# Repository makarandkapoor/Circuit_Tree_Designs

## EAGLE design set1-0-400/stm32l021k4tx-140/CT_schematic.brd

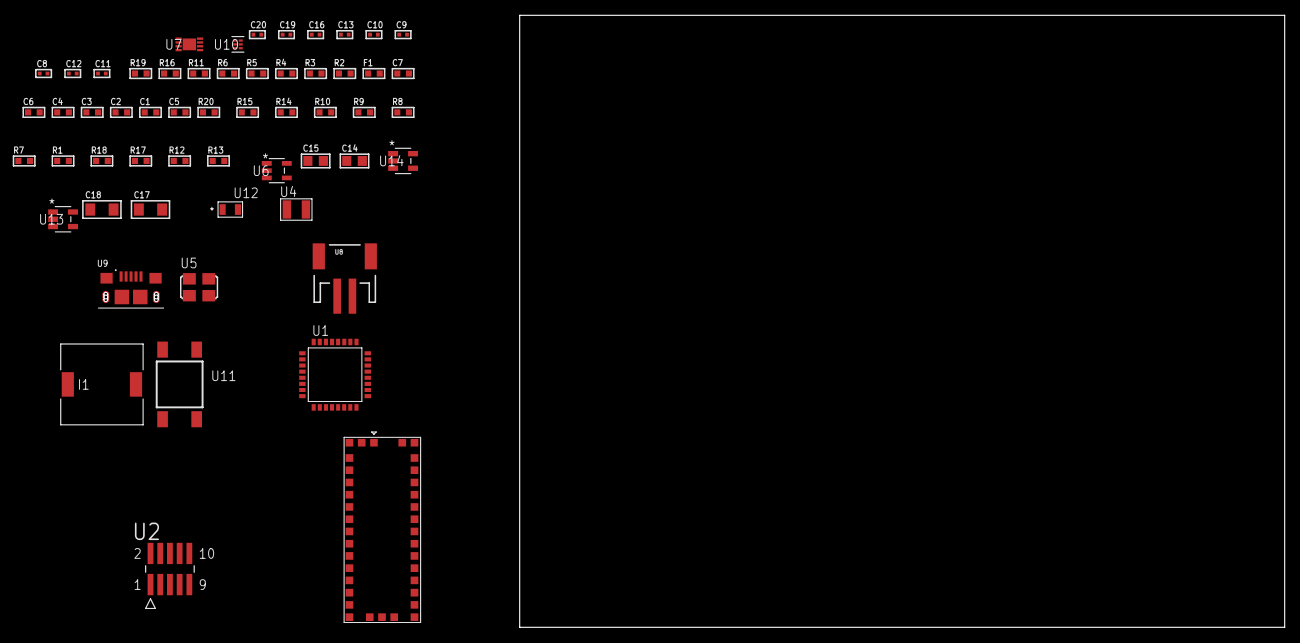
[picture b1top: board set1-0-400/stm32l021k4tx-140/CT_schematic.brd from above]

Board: 2 copper layers, 154.3 x 80.0 mm, 56 parts (0 on the bottom side), 26 nets, no tracks yet.

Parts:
C1, C2, C3, C4: 1e-07; C0603
C5: 4.7e-06; C0603
C6: 1e-08; C0603
C7: 1e-06; C0603
C8, C9: 1e-11; C0402
C10, C16: 1e-07; C0402
C11, C12: 2.2e-11; C0402
C13, C19, C20: 1e-08; C0402
C14, C15: 1e-05; C0805
C17, C18: 1e-05; C1206
F1: 240.0; L0603
I1: 3.8e-06; DR1040
R1, R7, R8, R9, R10, R14, R15, R20: 10000.0; R0603
R2: 1000.0; R0603
R3: 1600.5; R0603
R4: 4700.0; R0603
R5, R6: 2200.0; R0603
R11: 5.0; R0603
R12: 220000.0; R0603
R13: 1000000.0; R0603
R16: 9100.0; R0603
R17: 680000.0; R0603
R18: 120000.0; R0603
R19: 2000.0; R0603
U1: STM32L021K4T6; LQFP32
U2: FTSH-105-01-L-DV-K; SAMTEC_FTSH-105-01-L-DV-K
U3: M10382
U4: ABS07-32.768KHZ-7-T
U5: ASFL1-12MHZ-NCS; ASFL1
U6: ltc3406es5; TSOT-23-5
U7: MCP73831T-2ACI/MC; DFN8_2X3MC
U8: S2B-PH-SM4-TB(LF)(SN); JST-2-SMD
U9: 10118193-0001LF; FCI_10118193-0001LF
U10: TPS3895ADRYR; SON-6
U11: 4-1437565-2; SW_4-1437565-2
U12: Q65110A2395; LGM67K-G1J2-24-Z
U13, U14: nc7sz125m5x; NC7SZ125M5X

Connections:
CLK_CRYSTAL_U1_2: C8.1, U1.2, U4.1
CLK_CRYSTAL_U1_3: C9.1, U1.3, U4.2
CLK_U1_6: U1.6, U5.3
GND: C1.2, C2.2, C3.2, C4.2, C5.2, C6.2, C7.2, C8.2, C9.2, C10.2, C11.2, C12.2, C13.2, C14.2, C15.1, C15.2, C16.2, C17.2, C18.2, C19.2, C20.2, R2.2, R7.2, R11.2, R12.2, R16.2, R18.2, R19.2, U1.16, U1.32, U2.3, U2.5, U3.2, U3.4, U3.14, U3.17, U3.21, U3.24, U3.26, U3.28, U3.33, U3.34, U3.35, U3.36, U5.2, U6.2, U7.6, U7.9, U8.2, U9.5, U9.6, U9.7, U9.8, U9.9, U10.2, U12.C, U13.2, U13.3, U14.1, U14.3
INPUT_USBPOWER_5V: C17.1, R20.2, U7.1, U7.2, U9.1
NET_U1_4: R4.1, U1.4, U14.4
NET_U1_5: C6.1, C7.1, F1.1, U1.5
NET_U1_10: R5.1, U1.10, U3.19
NET_U1_20: R6.1, U1.20, U3.18
NET_U1_30: R3.1, U1.30, U12.A
NET_U1_31: R1.1, R7.1, U1.31, U11.3, U11.4
NET_U2_9: R11.1, U2.9
NET_U6_3: I1.1, U6.3
NET_U6_5: R12.1, R13.1, U6.5
NET_U6_ATNET_3: I1.2, R13.2
NET_U7_5: R20.1, U7.5
NET_U7_8: R19.1, U7.8
NET_U10_1: R15.1, R16.1, U10.1
NET_U10_3: R17.2, R18.1, U10.3
NET_U10_4: R14.1, U10.4, U13.4, U14.2
NET_U11_1: R2.1, U11.1, U11.2
PROC_SYS_SWCLK: R9.1, U1.24, U2.4
PROC_SYS_SWDIO: R10.1, U1.23, U2.2
RST_OUT_U2_JTAG_RST_B: R8.1, U2.10, U13.1
VCC_S1_3V7: C14.1, C18.1, U6.4, U7.3, U7.4, U8.1
VCC_TIER1_3V3: C1.1, C2.1, C3.1, C4.1, C5.1, C10.1, C11.1, C12.1, C13.1, C15.2, C16.1, C19.1, C20.1, F1.2, I1.2, R1.2, R3.2, R4.2, R5.2, R6.2, R8.2, R9.2, R10.2, R13.2, R14.2, R15.2, R17.1, U1.1, U1.17, U2.1, U3.5, U3.25, U3.27, U5.4, U10.6, U13.5, U14.5

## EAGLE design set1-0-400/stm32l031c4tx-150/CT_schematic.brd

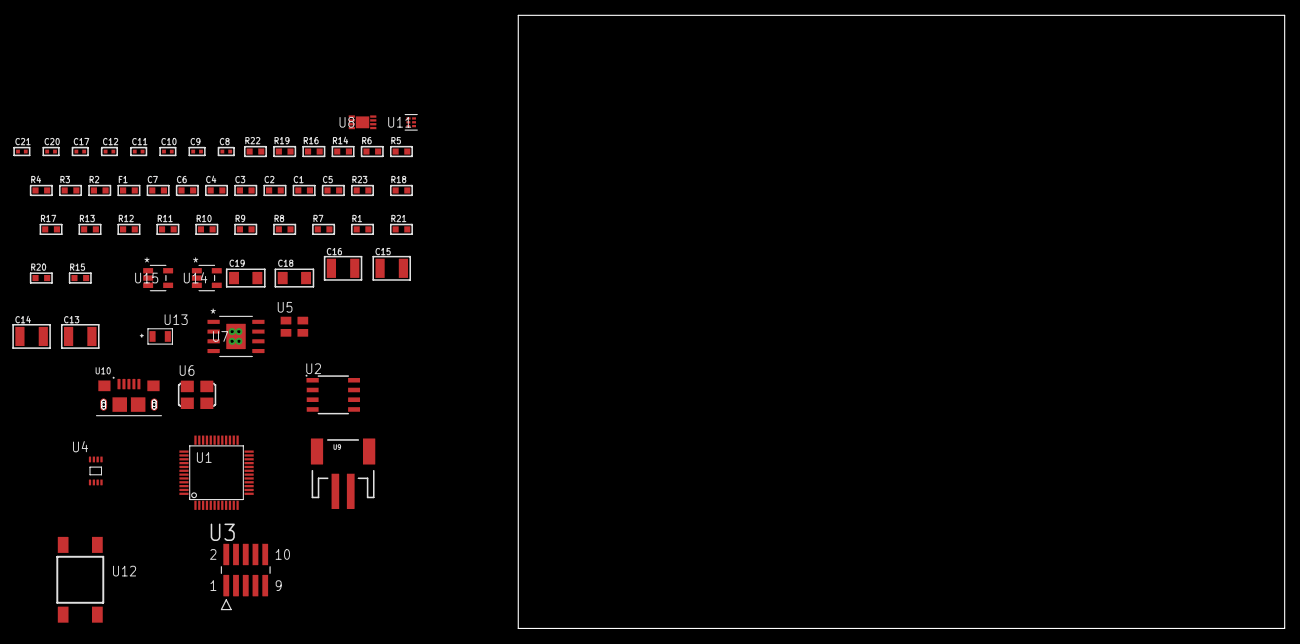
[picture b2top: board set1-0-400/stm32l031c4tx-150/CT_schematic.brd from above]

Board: 2 copper layers, 154.3 x 80.0 mm, 60 parts (0 on the bottom side), 30 nets, no tracks yet.

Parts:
C1, C2, C3, C4: 1e-07; C0603
C5: 4.7e-06; C0603
C6: 1e-08; C0603
C7: 1e-06; C0603
C8, C10, C11, C12, C20, C21: 1e-08; C0402
C9, C17: 1e-07; C0402
C13, C14, C15, C16: 1e-05; C1210
C18, C19: 1e-05; C1206
F1: 240.0; L0603
R1, R7, R8, R9, R10, R11, R12, R13, R17, R18, R23: 10000.0; R0603
R2: 1000.0; R0603
R3: 1600.5; R0603
R4: 4700.0; R0603
R5, R6, R16: 2200.0; R0603
R14: 5.0; R0603
R15: 4031.5447154472; R0603
R19: 9100.0; R0603
R20: 680000.0; R0603
R21: 120000.0; R0603
R22: 2000.0; R0603
U1: STM32L031C4T6; LQFP48
U2: AT25128B-SSHL-T; SOIC-8
U3: FTSH-105-01-L-DV-K; SAMTEC_FTSH-105-01-L-DV-K
U4: 24AA01T-I/MNY; TDFN-8/6MM
U5: ASEK-32.768KHz-ECST; ASEK
U6: ASFL1-25MHZ-NCS; ASFL1
U7: MIC5234YME; SOIC-8_EP
U8: MCP73831T-2ACI/MC; DFN8_2X3MC
U9: S2B-PH-SM4-TB(LF)(SN); JST-2-SMD
U10: 10118193-0001LF; FCI_10118193-0001LF
U11: TPS3895ADRYR; SON-6
U12: 4-1437565-2; SW_4-1437565-2
U13: Q65110A2395; LGM67K-G1J2-24-Z
U14, U15: nc7sz125m5x; NC7SZ125M5X

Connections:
CLK_U1_3: U1.3, U5.3
CLK_U1_5: U1.5, U6.3
GND: C1.2, C2.2, C3.2, C4.2, C5.2, C6.2, C7.2, C8.2, C9.2, C10.2, C11.2, C12.2, C13.2, C14.2, C15.2, C16.2, C17.2, C18.2, C19.2, C20.2, C21.2, R2.2, R7.2, R14.2, R16.2, R19.2, R21.2, R22.2, U1.8, U1.23, U1.35, U1.47, U2.4, U3.3, U3.5, U4.4, U4.7, U5.2, U6.2, U7.7, U7.EPAD, U8.6, U8.9, U9.2, U10.5, U10.6, U10.7, U10.8, U10.9, U11.2, U13.C, U14.2, U14.3, U15.1, U15.3
INPUT_USBPOWER_5V: C18.1, R23.2, U8.1, U8.2, U10.1
NET_U1_7: R4.1, U1.7, U15.4
NET_U1_9: C6.1, C7.1, F1.1, U1.9
NET_U1_30: R5.1, U1.30, U4.6
NET_U1_31: R6.1, U1.31, U4.5
NET_U1_44: R7.1, U1.44
NET_U1_45: R3.1, U1.45, U13.A
NET_U1_46: R1.1, U1.46, U12.3, U12.4
NET_U2_3: R8.1, U2.3
NET_U2_7: R10.1, U2.7
NET_U3_9: R14.1, U3.9
NET_U7_4: R15.2, R16.1, U7.4
NET_U8_5: R23.1, U8.5
NET_U8_8: R22.1, U8.8
NET_U11_1: R18.1, R19.1, U11.1
NET_U11_3: R20.2, R21.1, U11.3
NET_U11_4: R17.1, U11.4, U14.4, U15.2
NET_U12_1: R2.1, U12.1, U12.2
PROC_SPI1_MISO: U1.16, U2.2
PROC_SPI1_MOSI: U1.17, U2.5
PROC_SPI1_NSS: R9.1, U1.14, U2.1
PROC_SPI1_SCK: U1.15, U2.6
PROC_SYS_SWCLK: R12.1, U1.37, U3.4
PROC_SYS_SWDIO: R13.1, U1.34, U3.2
RST_OUT_U3_JTAG_RST_B: R11.1, U3.10, U14.1
VCC_S1_3V7: C13.1, C14.1, C19.1, U7.5, U7.8, U8.3, U8.4, U9.1
VCC_TIER1_3V3: C1.1, C2.1, C3.1, C4.1, C5.1, C8.1, C9.1, C10.1, C11.1, C12.1, C15.1, C16.1, C17.1, C20.1, C21.1, F1.2, R1.2, R3.2, R4.2, R5.2, R6.2, R8.2, R9.2, R10.2, R11.2, R12.2, R13.2, R15.1, R17.2, R18.2, R20.1, U1.24, U1.36, U1.48, U2.8, U3.1, U4.8, U5.4, U6.4, U7.1, U11.6, U14.5, U15.5

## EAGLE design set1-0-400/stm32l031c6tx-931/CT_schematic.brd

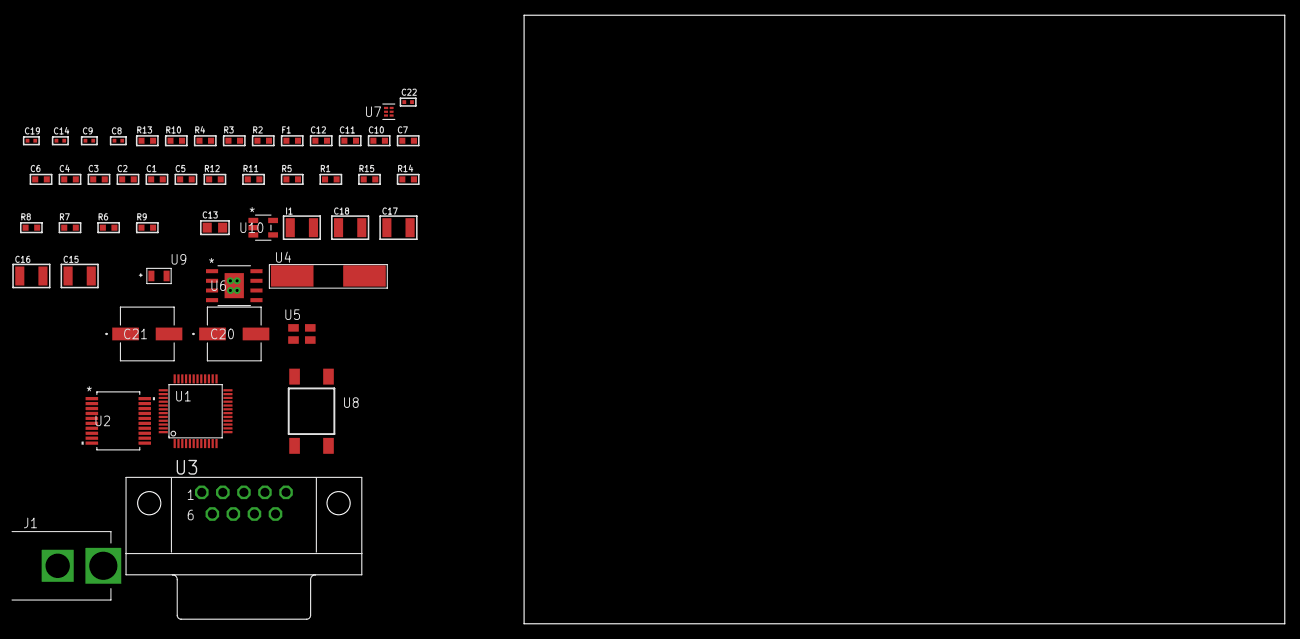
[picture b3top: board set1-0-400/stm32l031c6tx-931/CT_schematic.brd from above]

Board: 2 copper layers, 100.0 x 80.0 mm, 50 parts (0 on the bottom side), 32 nets, no tracks yet.

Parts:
C1, C2, C3, C4: 1e-07; C0603
C5: 4.7e-06; C0603
C6: 1e-08; C0603
C7, C10, C11, C12: 1e-06; C0603
C8, C9: 1e-11; C0402
C13: 4.7e-06; C0805
C14, C22: 1e-08; C0402
C15, C16, C17, C18: 1e-05; C1210
C19: 1e-07; C0402
C20, C21: 0.0001; EXV-9H
F1: 240.0; L0603
I1: 1.5e-05; L1210
J1: PJ-037B; PJ-037B_PACKAGE
R1, R5, R11, R12: 10000.0; R0603
R2: 1000.0; R0603
R3: 1600.5; R0603
R4: 4700.0; R0603
R6, R7, R8: 100000.0; R0603
R9: 4031.5447154472; R0603
R10: 2200.0; R0603
R13: 9100.0; R0603
R14: 680000.0; R0603
R15: 120000.0; R0603
U1: STM32L031C6T7; LQFP48
U2: MAX3218EAP+T; SSOP-20
U3: 182-009-113R531; 182-009-MALE
U4: ABLS-25.000MHZ-B2F-T
U5: ASEK-32.768KHz-ECST; ASEK
U6: MIC5234YME; SOIC-8_EP
U7: TPS3895ADRYR; SON-6
U8: 4-1437565-2; SW_4-1437565-2
U9: Q65110A2395; LGM67K-G1J2-24-Z
U10: nc7sz125m5x; NC7SZ125M5X

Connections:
CLK_CRYSTAL_U1_5: C8.1, U1.5, U4.1
CLK_CRYSTAL_U1_6: C9.1, U1.6, U4.2
CLK_U1_3: U1.3, U5.3
GND: C1.2, C2.2, C3.2, C4.2, C5.2, C6.2, C7.2, C8.2, C9.2, C10.2, C11.2, C12.2, C14.2, C15.2, C16.2, C17.2, C18.2, C19.2, C20.2, C21.2, C22.2, J1.2, R2.2, R5.2, R10.2, R13.2, R15.2, U1.8, U1.23, U1.35, U1.47, U2.5, U2.17, U2.20, U3.5, U5.2, U6.7, U6.EPAD, U7.2, U9.C, U10.1, U10.3
NET_U1_7: R4.1, U1.7, U10.4
NET_U1_9: C6.1, C7.1, F1.1, U1.9
NET_U1_44: R5.1, U1.44
NET_U1_45: R3.1, U1.45, U9.A
NET_U1_46: R1.1, U1.46, U8.3, U8.4
NET_U2_1: I1.1, U2.1
NET_U2_2: R6.1, U2.2
NET_U2_3: R7.1, U2.3
NET_U2_4: R8.1, U2.4
NET_U2_15: C12.1, U2.15
NET_U2_16: C13.2, U2.16
NET_U2_18: C13.1, U2.18
NET_U2_19: C11.1, U2.19
NET_U3_2: U2.12, U3.2
NET_U3_3: U2.14, U3.3
NET_U3_7: U2.11, U3.7
NET_U3_8: U2.13, U3.8
NET_U6_4: R9.2, R10.1, U6.4
NET_U7_1: R12.1, R13.1, U7.1
NET_U7_3: R14.2, R15.1, U7.3
NET_U7_4: R11.1, U7.4, U10.2
NET_U8_1: R2.1, U8.1, U8.2
PROC_LPUART1_CTS: U1.16, U2.8
PROC_LPUART1_RTS: U1.19, U2.10
PROC_LPUART1_RX: U1.1, U2.9
PROC_LPUART1_TX: U1.12, U2.7
VCC_S1_10V9: C15.1, C16.1, C20.1, C21.1, J1.1, U6.5, U6.8
VCC_TIER1_3V3: C1.1, C2.1, C3.1, C4.1, C5.1, C10.1, C14.1, C17.1, C18.1, C19.1, C22.1, F1.2, I1.2, R1.2, R3.2, R4.2, R6.2, R7.2, R8.2, R9.1, R11.2, R12.2, R14.1, U1.24, U1.36, U1.48, U2.6, U5.4, U6.1, U7.6, U10.5

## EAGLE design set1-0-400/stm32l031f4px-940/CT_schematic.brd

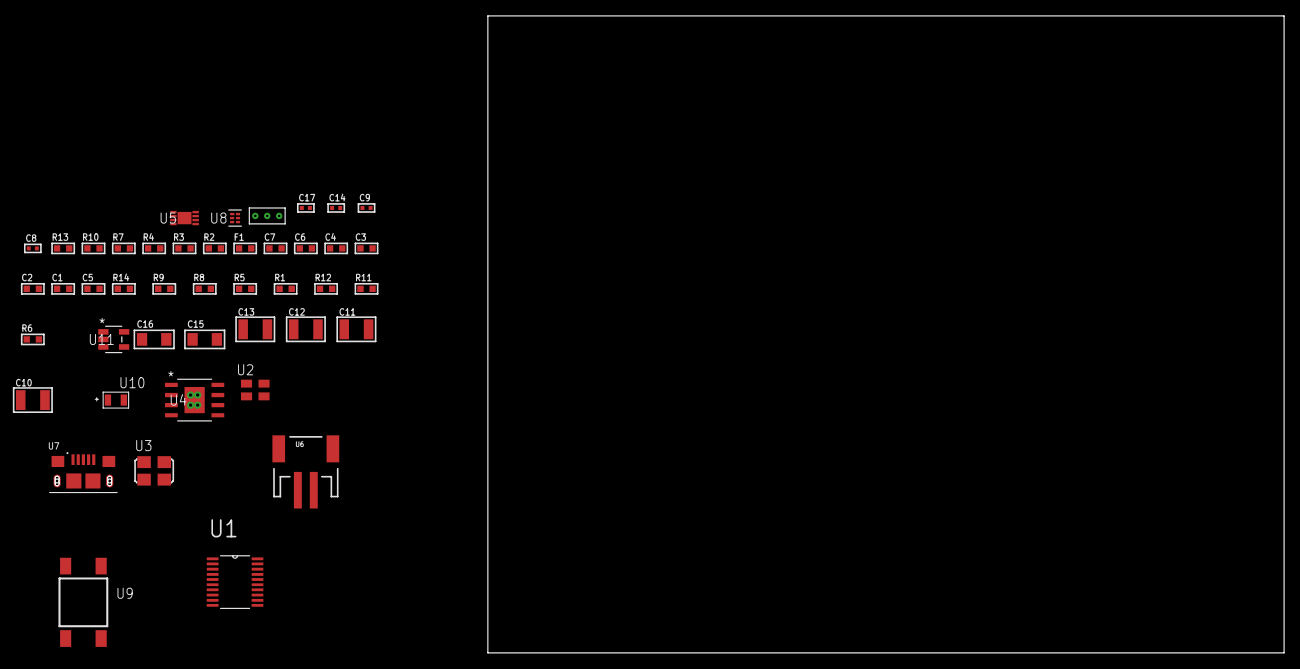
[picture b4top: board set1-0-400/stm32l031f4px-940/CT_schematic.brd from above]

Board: 2 copper layers, 154.3 x 80.0 mm, 44 parts (0 on the bottom side), 20 nets, no tracks yet.

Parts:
C1, C2, C3, C4: 1e-07; C0603
C5: 4.7e-06; C0603
C6: 1e-08; C0603
C7: 1e-06; C0603
C8, C9, C17: 1e-08; C0402
C10, C11, C12, C13: 1e-05; C1210
C14: 1e-07; C0402
C15, C16: 1e-05; C1206
F1: 240.0; L0603
R1, R5, R8, R9, R14: 10000.0; R0603
R2: 1000.0; R0603
R3: 1600.5; R0603
R4: 4700.0; R0603
R6: 4031.5447154472; R0603
R7: 2200.0; R0603
R10: 9100.0; R0603
R11: 680000.0; R0603
R12: 120000.0; R0603
R13: 2000.0; R0603
U1: STM32L031F4P6; TSSOP20
U2: ASEK-32.768KHz-ECST; ASEK
U3: ASFL1-12MHZ-NCS; ASFL1
U4: MIC5234YME; SOIC-8_EP
U5: MCP73831T-2ACI/MC; DFN8_2X3MC
U6: S2B-PH-SM4-TB(LF)(SN); JST-2-SMD
U7: 10118193-0001LF; FCI_10118193-0001LF
U8: TPS3895ADRYR; SON-6
U9: 4-1437565-2; SW_4-1437565-2
U10: Q65110A2395; LGM67K-G1J2-24-Z
U11: nc7sz125m5x; NC7SZ125M5X
U12: Dummy; DUMMY_PACKAGE_90

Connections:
CLK_U1_2: U1.2, U2.3
CLK_U1_6: U1.6, U3.3
GND: C1.2, C2.2, C3.2, C4.2, C5.2, C6.2, C7.2, C8.2, C9.2, C10.2, C11.2, C12.2, C13.2, C14.2, C15.2, C16.2, C17.2, R2.2, R5.2, R7.2, R10.2, R12.2, R13.2, U1.15, U2.2, U3.2, U4.7, U4.EPAD, U5.6, U5.9, U6.2, U7.5, U7.6, U7.7, U7.8, U7.9, U8.2, U10.C, U11.1, U11.3, U12.1
INPUT_USBPOWER_5V: C15.1, R14.2, U5.1, U5.2, U7.1
NET_U1_1: R5.1, U1.1
NET_U1_4: R4.1, U1.4, U11.4
NET_U1_5: C6.1, C7.1, F1.1, U1.5
NET_U1_19: R3.1, U1.19, U10.A
NET_U1_20: R1.1, U1.20, U9.3, U9.4
NET_U4_4: R6.2, R7.1, U4.4
NET_U5_5: R14.1, U5.5
NET_U5_8: R13.1, U5.8
NET_U8_1: R9.1, R10.1, U8.1
NET_U8_3: R11.2, R12.1, U8.3
NET_U8_4: R8.1, U8.4, U11.2
NET_U9_1: R2.1, U9.1, U9.2
PROC_TIM2_CH3: U1.8, U12.3
PROC_TIM2_CH4: U1.9, U12.2
VCC_S1_3V7: C10.1, C11.1, C16.1, U4.5, U4.8, U5.3, U5.4, U6.1
VCC_TIER1_3V3: C1.1, C2.1, C3.1, C4.1, C5.1, C8.1, C9.1, C12.1, C13.1, C14.1, C17.1, F1.2, R1.2, R3.2, R4.2, R6.1, R8.2, R9.2, R11.1, U1.16, U2.4, U3.4, U4.1, U8.6, U11.5

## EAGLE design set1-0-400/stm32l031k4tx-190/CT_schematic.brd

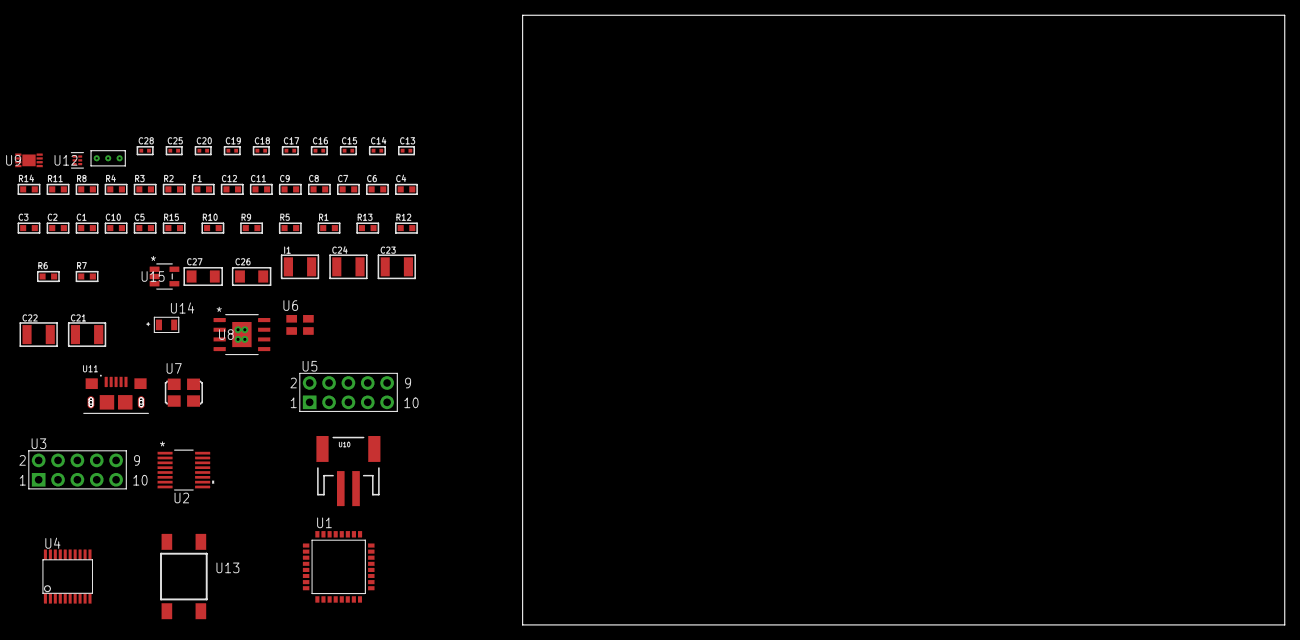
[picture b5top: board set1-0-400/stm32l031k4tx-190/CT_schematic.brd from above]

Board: 2 copper layers, 156.9 x 80.0 mm, 61 parts (0 on the bottom side), 47 nets, no tracks yet.

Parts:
C1, C2, C3, C4: 1e-07; C0603
C5: 4.7e-06; C0603
C6: 1e-08; C0603
C7, C8, C9, C11, C12: 1e-06; C0603
C10: 2.2e-07; C0603
C13, C14, C15, C16, C17, C18, C25: 1e-07; C0402
C19, C20, C28: 1e-08; C0402
C21, C22, C23, C24: 1e-05; C1210
C26, C27: 1e-05; C1206
F1: 240.0; L0603
I1: 1e-05; L1210
R1, R5, R9, R10, R15: 10000.0; R0603
R2: 1000.0; R0603
R3: 1600.5; R0603
R4: 4700.0; R0603
R6: 100000.0; R0603
R7: 4031.5447154472; R0603
R8: 2200.0; R0603
R11: 9100.0; R0603
R12: 680000.0; R0603
R13: 120000.0; R0603
R14: 2000.0; R0603
U1: STM32L031K4T6; LQFP32
U2: LTC2804CGN-1#PBF; SSOP-16
U3, U5: HTSS-105-01-G-D
U4: SP3203ECY-L/TR; TSSOP20-I
U6: ASEK-32.768KHz-ECST; ASEK
U7: ASFL1-12MHZ-NCS; ASFL1
U8: MIC5234YME; SOIC-8_EP
U9: MCP73831T-2ACI/MC; DFN8_2X3MC
U10: S2B-PH-SM4-TB(LF)(SN); JST-2-SMD
U11: 10118193-0001LF; FCI_10118193-0001LF
U12: TPS3895ADRYR; SON-6
U13: 4-1437565-2; SW_4-1437565-2
U14: Q65110A2395; LGM67K-G1J2-24-Z
U15: nc7sz125m5x; NC7SZ125M5X
U16: Dummy; DUMMY_PACKAGE_126

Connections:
CLK_U1_2: U1.2, U6.3
CLK_U1_6: U1.6, U7.3
GND: C1.2, C2.2, C3.2, C4.2, C5.2, C6.2, C7.2, C8.2, C9.2, C11.2, C12.2, C13.2, C14.2, C17.2, C18.2, C19.2, C20.2, C21.2, C22.2, C23.2, C24.2, C25.2, C26.2, C27.2, C28.2, R2.2, R5.2, R8.2, R11.2, R13.2, R14.2, U1.16, U1.32, U2.8, U3.9, U4.18, U5.9, U6.2, U7.2, U8.7, U8.EPAD, U9.6, U9.9, U10.2, U11.5, U11.6, U11.7, U11.8, U11.9, U12.2, U14.C, U15.1, U15.3, U16.1
INPUT_USBPOWER_5V: C26.1, R15.2, U9.1, U9.2, U11.1
NET_U1_4: R4.1, U1.4, U15.4
NET_U1_5: C6.1, C7.1, F1.1, U1.5
NET_U1_29: R3.1, U1.29, U14.A
NET_U1_30: R1.1, U1.30, U13.3, U13.4
NET_U1_31: R5.1, U1.31
NET_U2_6: C8.1, U2.6
NET_U2_7: C10.1, I1.2, U2.7
NET_U2_9: C9.1, U2.9
NET_U2_10: C10.2, U2.10
NET_U2_11: R6.1, U2.11
NET_U3_3: U2.1, U3.3
NET_U3_4: U2.2, U3.4
NET_U3_5: U2.3, U3.5
NET_U3_6: U2.4, U3.6
NET_U4_1: C15.1, U4.1
NET_U4_2: C17.1, U4.2
NET_U4_3: C15.2, U4.3
NET_U4_4: C16.1, U4.4
NET_U4_5: C16.2, U4.5
NET_U4_6: C18.1, U4.6
NET_U5_3: U4.14, U5.3
NET_U5_4: U4.13, U5.4
NET_U5_5: U4.17, U5.5
NET_U5_6: U4.16, U5.6
NET_U8_4: R7.2, R8.1, U8.4
NET_U9_5: R15.1, U9.5
NET_U9_8: R14.1, U9.8
NET_U12_1: R10.1, R11.1, U12.1
NET_U12_3: R12.2, R13.1, U12.3
NET_U12_4: R9.1, U12.4, U15.2
NET_U13_1: R2.1, U13.1, U13.2
PROC_ADC_IN4: U1.10, U16.2
PROC_ADC_IN5: U1.11, U16.3
PROC_LPUART1_CTS: U1.12, U2.13
PROC_LPUART1_RTS: U1.15, U2.15
PROC_LPUART1_RX: U1.9, U2.16
PROC_LPUART1_TX: U1.8, U2.14
PROC_USART2_CTS: U1.13, U4.8
PROC_USART2_RTS: U1.7, U4.10
PROC_USART2_RX: U1.20, U4.11
PROC_USART2_TX: U1.19, U4.7
VCC_S1_3V7: C21.1, C22.1, C27.1, U8.5, U8.8, U9.3, U9.4, U10.1
VCC_TIER1_3V3: C1.1, C2.1, C3.1, C4.1, C5.1, C11.1, C12.1, C13.1, C14.1, C19.1, C20.1, C23.1, C24.1, C25.1, C28.1, F1.2, I1.1, R1.2, R3.2, R4.2, R6.2, R7.1, R9.2, R10.2, R12.1, U1.1, U1.17, U2.5, U2.12, U4.12, U4.19, U6.4, U7.4, U8.1, U12.6, U15.5

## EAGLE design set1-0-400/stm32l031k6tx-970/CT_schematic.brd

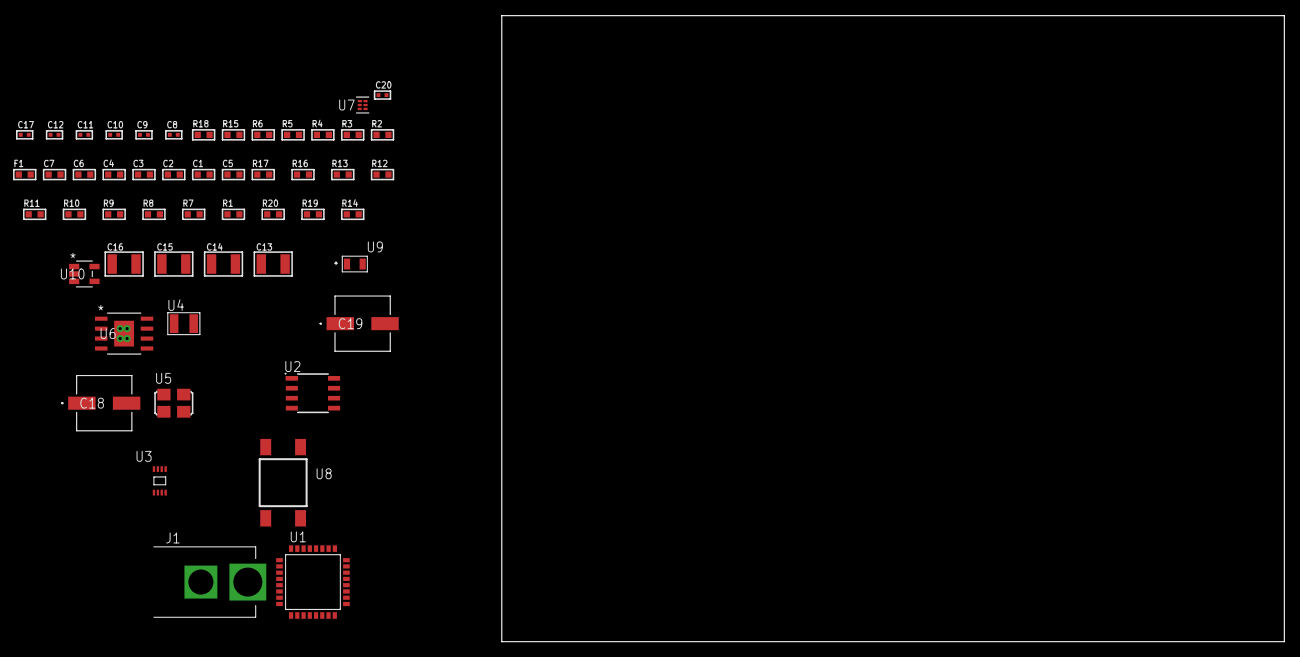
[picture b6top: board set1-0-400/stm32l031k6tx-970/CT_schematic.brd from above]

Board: 2 copper layers, 100.0 x 80.0 mm, 52 parts (0 on the bottom side), 27 nets, no tracks yet.

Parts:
C1, C2, C3, C4: 1e-07; C0603
C5: 4.7e-06; C0603
C6: 1e-08; C0603
C7: 1e-06; C0603
C8, C9: 1e-11; C0402
C10, C11, C12, C20: 1e-08; C0402
C13, C14, C15, C16: 1e-05; C1210
C17: 1e-07; C0402
C18, C19: 0.0001; EXV-9H
F1: 240.0; L0603
J1: PJ-037B; PJ-037B_PACKAGE
R1, R7, R8, R9, R10, R11, R12, R13, R16, R17: 10000.0; R0603
R2: 1000.0; R0603
R3: 1600.5; R0603
R4: 4700.0; R0603
R5, R6, R15: 2200.0; R0603
R14: 4031.5447154472; R0603
R18: 9100.0; R0603
R19: 680000.0; R0603
R20: 120000.0; R0603
U1: STM32L031K6T6; LQFP32
U2: AT25160B-SSHL-T; SOIC-8
U3: 24AA32AT-I/MNY; TDFN-8/6MM
U4: ABS07-32.768KHZ-7-T
U5: ASFL1-12MHZ-NCS; ASFL1
U6: MIC5234YME; SOIC-8_EP
U7: TPS3895ADRYR; SON-6
U8: 4-1437565-2; SW_4-1437565-2
U9: Q65110A2395; LGM67K-G1J2-24-Z
U10: nc7sz125m5x; NC7SZ125M5X

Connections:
CLK_CRYSTAL_U1_2: C8.1, U1.2, U4.1
CLK_CRYSTAL_U1_3: C9.1, U1.3, U4.2
CLK_U1_6: U1.6, U5.3
GND: C1.2, C2.2, C3.2, C4.2, C5.2, C6.2, C7.2, C8.2, C9.2, C10.2, C11.2, C12.2, C13.2, C14.2, C15.2, C16.2, C17.2, C18.2, C19.2, C20.2, J1.2, R2.2, R7.2, R11.2, R15.2, R18.2, R20.2, U1.16, U1.32, U2.4, U3.4, U3.7, U5.2, U6.7, U6.EPAD, U7.2, U9.C, U10.1, U10.3
NET_U1_4: R4.1, U1.4, U10.4
NET_U1_5: C6.1, C7.1, F1.1, U1.5
NET_U1_19: R5.1, U1.19, U3.6
NET_U1_20: R6.1, U1.20, U3.5
NET_U1_29: R3.1, U1.29, U9.A
NET_U1_30: R1.1, U1.30, U8.3, U8.4
NET_U1_31: R7.1, U1.31
NET_U2_3: R8.1, U2.3
NET_U2_7: R10.1, U2.7
NET_U3_1: R11.1, U3.1
NET_U3_2: R12.1, U3.2
NET_U3_3: R13.1, U3.3
NET_U6_4: R14.2, R15.1, U6.4
NET_U7_1: R17.1, R18.1, U7.1
NET_U7_3: R19.2, R20.1, U7.3
NET_U7_4: R16.1, U7.4, U10.2
NET_U8_1: R2.1, U8.1, U8.2
PROC_SPI1_MISO: U1.12, U2.2
PROC_SPI1_MOSI: U1.13, U2.5
PROC_SPI1_NSS: R9.1, U1.10, U2.1
PROC_SPI1_SCK: U1.11, U2.6
VCC_S1_4V8: C13.1, C14.1, C18.1, C19.1, J1.1, U6.5, U6.8
VCC_TIER1_3V3: C1.1, C2.1, C3.1, C4.1, C5.1, C10.1, C11.1, C12.1, C15.1, C16.1, C17.1, C20.1, F1.2, R1.2, R3.2, R4.2, R5.2, R6.2, R8.2, R9.2, R10.2, R12.2, R13.2, R14.1, R16.2, R17.2, R19.1, U1.1, U1.17, U2.8, U3.8, U5.4, U6.1, U7.6, U10.5

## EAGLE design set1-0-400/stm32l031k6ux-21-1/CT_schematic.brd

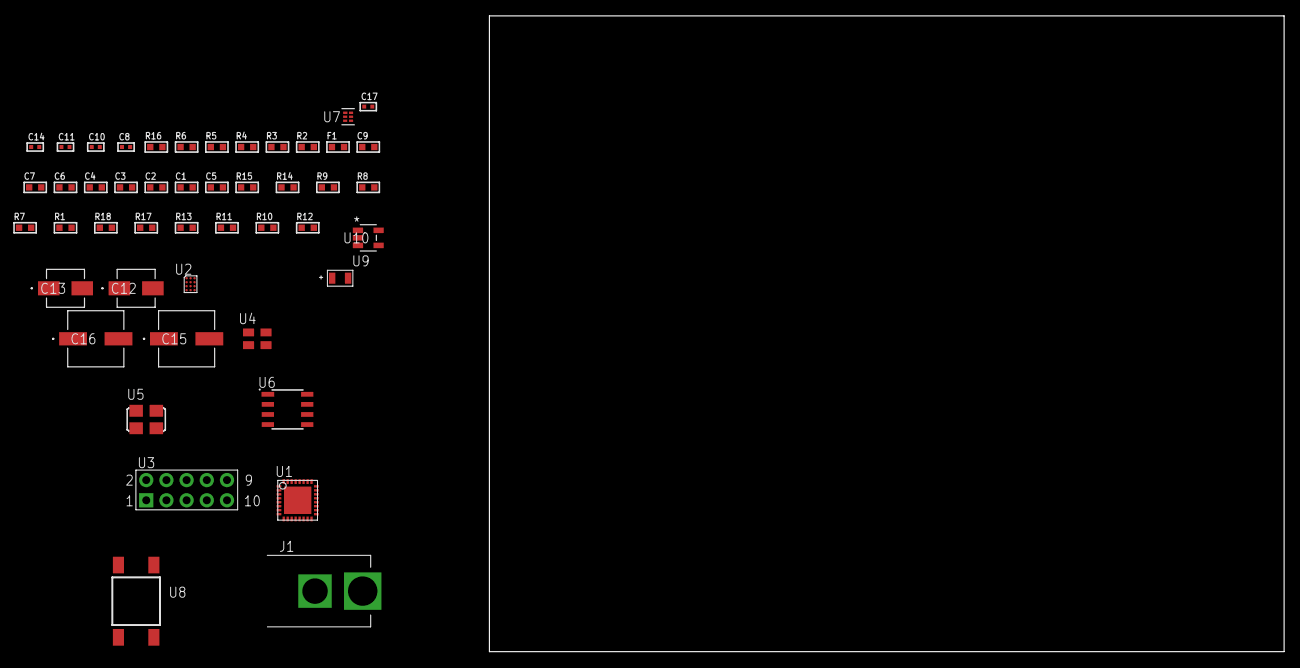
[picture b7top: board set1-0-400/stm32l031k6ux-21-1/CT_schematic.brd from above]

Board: 2 copper layers, 100.0 x 80.0 mm, 47 parts (0 on the bottom side), 25 nets, no tracks yet.

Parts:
C1, C2, C3, C4: 1e-07; C0603
C5: 4.7e-06; C0603
C6: 1e-08; C0603
C7, C9: 1e-06; C0603
C8, C14: 1e-07; C0402
C10, C11, C17: 1e-08; C0402
C12: 1e-06; EXV-9B
C13: 2.2e-06; EXV-9B
C15, C16: 0.0001; EXV-9H
F1: 240.0; L0603
J1: PJ-037B; PJ-037B_PACKAGE
R1, R7, R8, R9, R14, R15: 10000.0; R0603
R2: 1000.0; R0603
R3: 1600.5; R0603
R4: 4700.0; R0603
R5, R6: 2200.0; R0603
R10, R11, R13: 100000.0; R0603
R12: 164658.62; R0603
R16: 9100.0; R0603
R17: 680000.0; R0603
R18: 120000.0; R0603
U1: STM32L031K6U7; UFQFPN32
U2: TSC2014IYZGT
U3: HTSS-105-01-G-D
U4: ASEK-32.768KHz-ECST; ASEK
U5: ASFL1-12MHZ-NCS; ASFL1
U6: LP2954AIMX/NOPB; LP2954
U7: TPS3895ADRYR; SON-6
U8: 4-1437565-2; SW_4-1437565-2
U9: Q65110A2395; LGM67K-G1J2-24-Z
U10: nc7sz125m5x; NC7SZ125M5X

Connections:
CLK_U1_2: U1.2, U4.3
CLK_U1_6: U1.6, U5.3
GND: C1.2, C2.2, C3.2, C4.2, C5.2, C6.2, C7.2, C8.2, C9.2, C10.2, C11.2, C12.2, C13.2, C14.2, C15.2, C16.2, C17.2, J1.2, R2.2, R7.2, R13.2, R16.2, R18.2, U1.EPAD, U2.D2, U3.9, U4.2, U5.2, U6.4, U7.2, U9.C, U10.1, U10.3
NET_U1_4: R4.1, U1.4, U10.4
NET_U1_5: C6.1, C7.1, F1.1, U1.5
NET_U1_19: R5.1, U1.19, U2.D1
NET_U1_20: R6.1, U1.20, U2.C1
NET_U1_30: R3.1, U1.30, U9.A
NET_U1_31: R7.1, U1.31
NET_U1_32: R1.1, U1.32, U8.3, U8.4
NET_U2_B1: R9.1, U2.B1
NET_U2_C2: R8.1, U2.C2
NET_U3_3: U2.B3, U3.3
NET_U3_4: U2.D3, U3.4
NET_U3_5: U2.A3, U3.5
NET_U3_6: U2.C3, U3.6
NET_U6_3: R11.1, U6.3
NET_U6_5: R10.1, U6.5
NET_U6_7: R12.2, R13.1, U6.7
NET_U7_1: R15.1, R16.1, U7.1
NET_U7_3: R17.2, R18.1, U7.3
NET_U7_4: R14.1, U7.4, U10.2
NET_U8_1: R2.1, U8.1, U8.2
VCC_S1_16V3: C12.1, C15.1, C16.1, J1.1, R11.2, U6.8
VCC_TIER1_3V3: C1.1, C2.1, C3.1, C4.1, C5.1, C8.1, C9.1, C10.1, C11.1, C13.1, C14.1, C17.1, F1.2, R1.2, R3.2, R4.2, R5.2, R6.2, R8.2, R9.2, R10.2, R12.1, R14.2, R15.2, R17.1, U1.1, U1.17, U2.A2, U2.B2, U4.4, U5.4, U6.1, U7.6, U10.5

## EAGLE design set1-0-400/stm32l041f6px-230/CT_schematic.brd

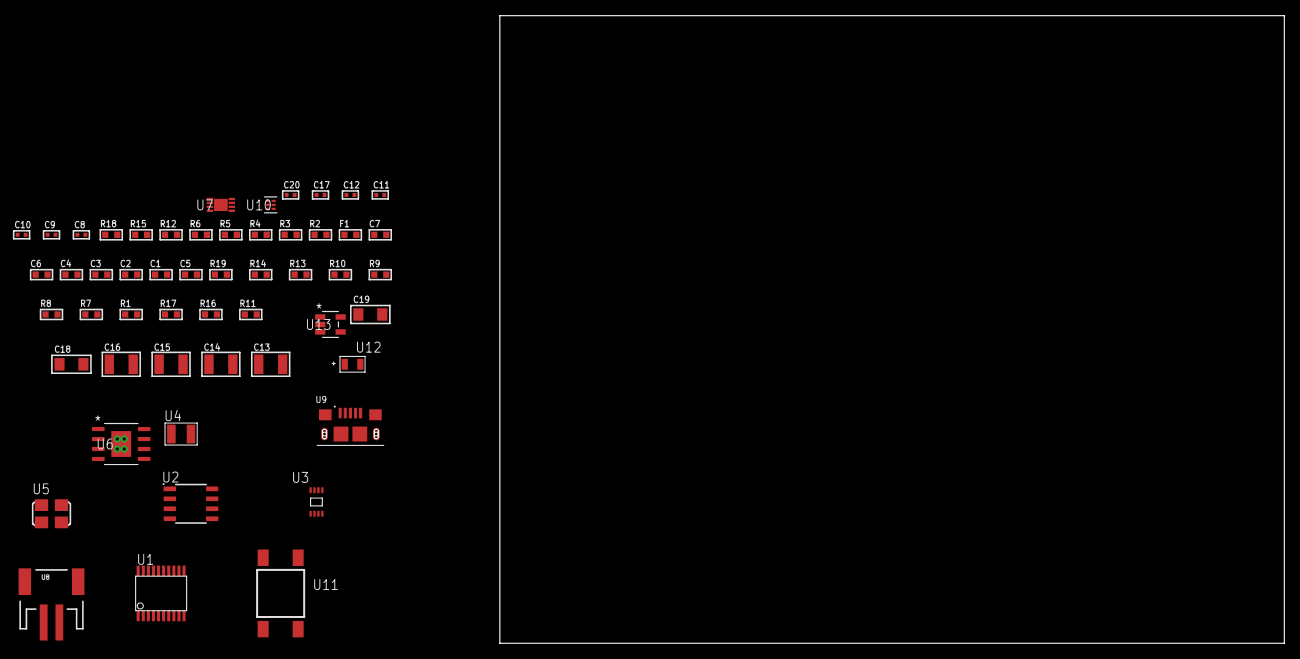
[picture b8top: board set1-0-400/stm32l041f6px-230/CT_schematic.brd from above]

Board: 2 copper layers, 122.6 x 80.0 mm, 53 parts (0 on the bottom side), 27 nets, no tracks yet.

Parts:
C1, C2, C3, C4: 1e-07; C0603
C5: 4.7e-06; C0603
C6: 1e-08; C0603
C7: 1e-06; C0603
C8, C9: 1e-11; C0402
C10, C11, C12, C20: 1e-08; C0402
C13, C14, C15, C16: 1e-05; C1210
C17: 1e-07; C0402
C18, C19: 1e-05; C1206
F1: 240.0; L0603
R1, R7, R8, R9, R10, R13, R14, R19: 10000.0; R0603
R2: 1000.0; R0603
R3: 1600.5; R0603
R4: 4700.0; R0603
R5, R6, R12: 2200.0; R0603
R11: 4031.5447154472; R0603
R15: 9100.0; R0603
R16: 680000.0; R0603
R17: 120000.0; R0603
R18: 2000.0; R0603
U1: STM32L041F6P7; TSSOP20-I
U2: AT25256B-SSHL-T; SOIC-8
U3: 24AA01T-I/MNY; TDFN-8/6MM
U4: ABS07-32.768KHZ-7-T
U5: ASFL1-12MHZ-NCS; ASFL1
U6: MIC5234YME; SOIC-8_EP
U7: MCP73831T-2ACI/MC; DFN8_2X3MC
U8: S2B-PH-SM4-TB(LF)(SN); JST-2-SMD
U9: 10118193-0001LF; FCI_10118193-0001LF
U10: TPS3895ADRYR; SON-6
U11: 4-1437565-2; SW_4-1437565-2
U12: Q65110A2395; LGM67K-G1J2-24-Z
U13: nc7sz125m5x; NC7SZ125M5X

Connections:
CLK_CRYSTAL_U1_2: C8.1, U1.2, U4.1
CLK_CRYSTAL_U1_3: C9.1, U1.3, U4.2
CLK_U1_6: U1.6, U5.3
GND: C1.2, C2.2, C3.2, C4.2, C5.2, C6.2, C7.2, C8.2, C9.2, C10.2, C11.2, C12.2, C13.2, C14.2, C15.2, C16.2, C17.2, C18.2, C19.2, C20.2, R2.2, R7.2, R12.2, R15.2, R17.2, R18.2, U1.15, U2.4, U3.4, U5.2, U6.7, U6.EPAD, U7.6, U7.9, U8.2, U9.5, U9.6, U9.7, U9.8, U9.9, U10.2, U12.C, U13.1, U13.3
INPUT_USBPOWER_5V: C18.1, R19.2, U7.1, U7.2, U9.1
NET_U1_1: R7.1, U1.1
NET_U1_4: R4.1, U1.4, U13.4
NET_U1_5: C6.1, C7.1, F1.1, U1.5
NET_U1_17: R5.1, U1.17, U3.6
NET_U1_18: R6.1, U1.18, U3.5
NET_U1_19: R3.1, U1.19, U12.A
NET_U1_20: R1.1, U1.20, U11.3, U11.4
NET_U2_3: R8.1, U2.3
NET_U2_7: R10.1, U2.7
NET_U6_4: R11.2, R12.1, U6.4
NET_U7_5: R19.1, U7.5
NET_U7_8: R18.1, U7.8
NET_U10_1: R14.1, R15.1, U10.1
NET_U10_3: R16.2, R17.1, U10.3
NET_U10_4: R13.1, U10.4, U13.2
NET_U11_1: R2.1, U11.1, U11.2
PROC_SPI1_MISO: U1.12, U2.2
PROC_SPI1_MOSI: U1.13, U2.5
PROC_SPI1_NSS: R9.1, U1.10, U2.1
PROC_SPI1_SCK: U1.11, U2.6
VCC_S1_3V7: C13.1, C14.1, C19.1, U6.5, U6.8, U7.3, U7.4, U8.1
VCC_TIER1_3V3: C1.1, C2.1, C3.1, C4.1, C5.1, C10.1, C11.1, C12.1, C15.1, C16.1, C17.1, C20.1, F1.2, R1.2, R3.2, R4.2, R5.2, R6.2, R8.2, R9.2, R10.2, R11.1, R13.2, R14.2, R16.1, U1.16, U2.8, U3.7, U3.8, U5.4, U6.1, U10.6, U13.5
